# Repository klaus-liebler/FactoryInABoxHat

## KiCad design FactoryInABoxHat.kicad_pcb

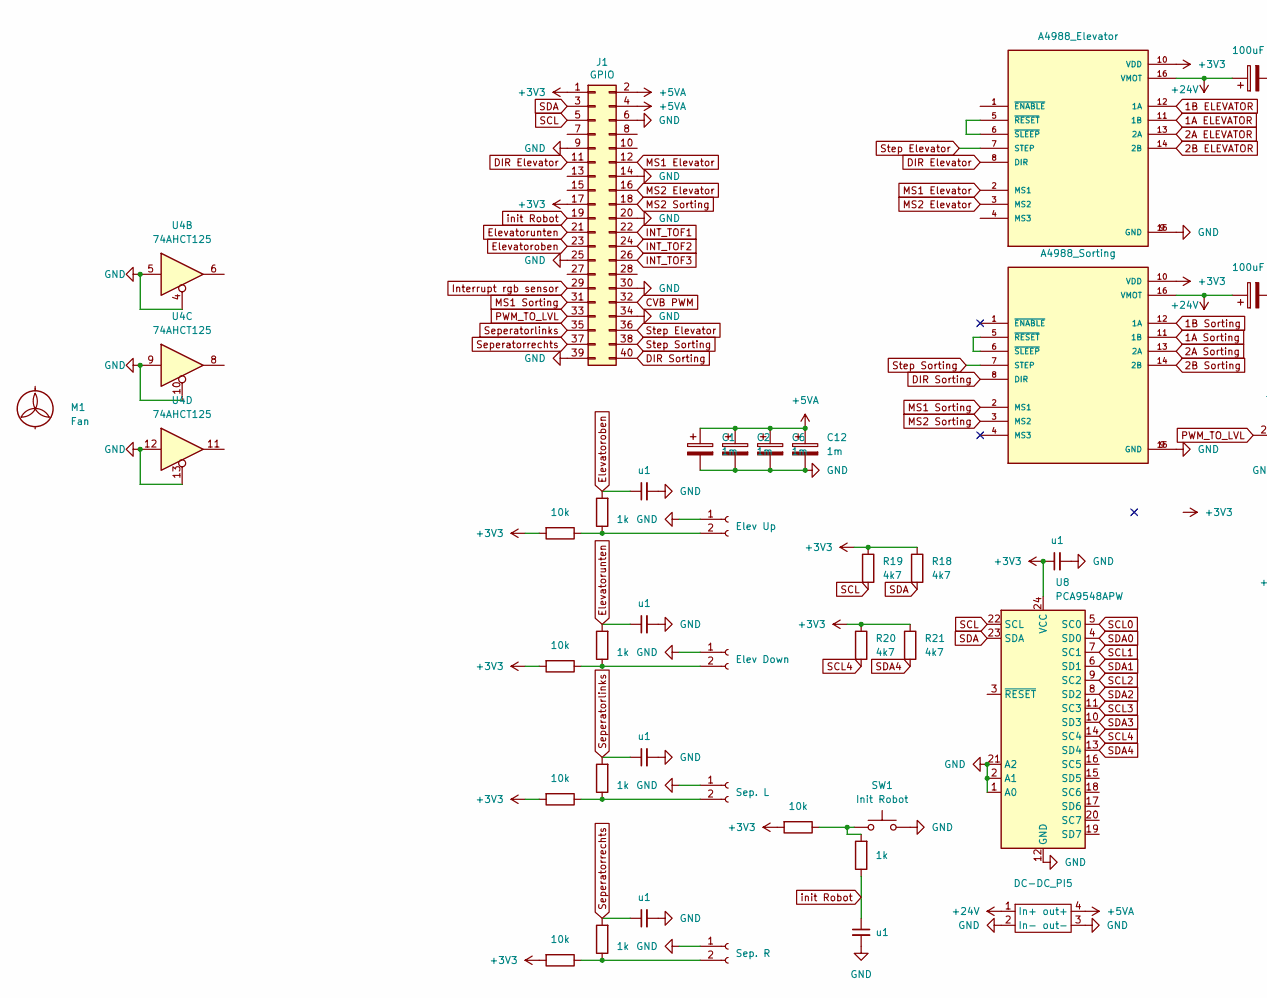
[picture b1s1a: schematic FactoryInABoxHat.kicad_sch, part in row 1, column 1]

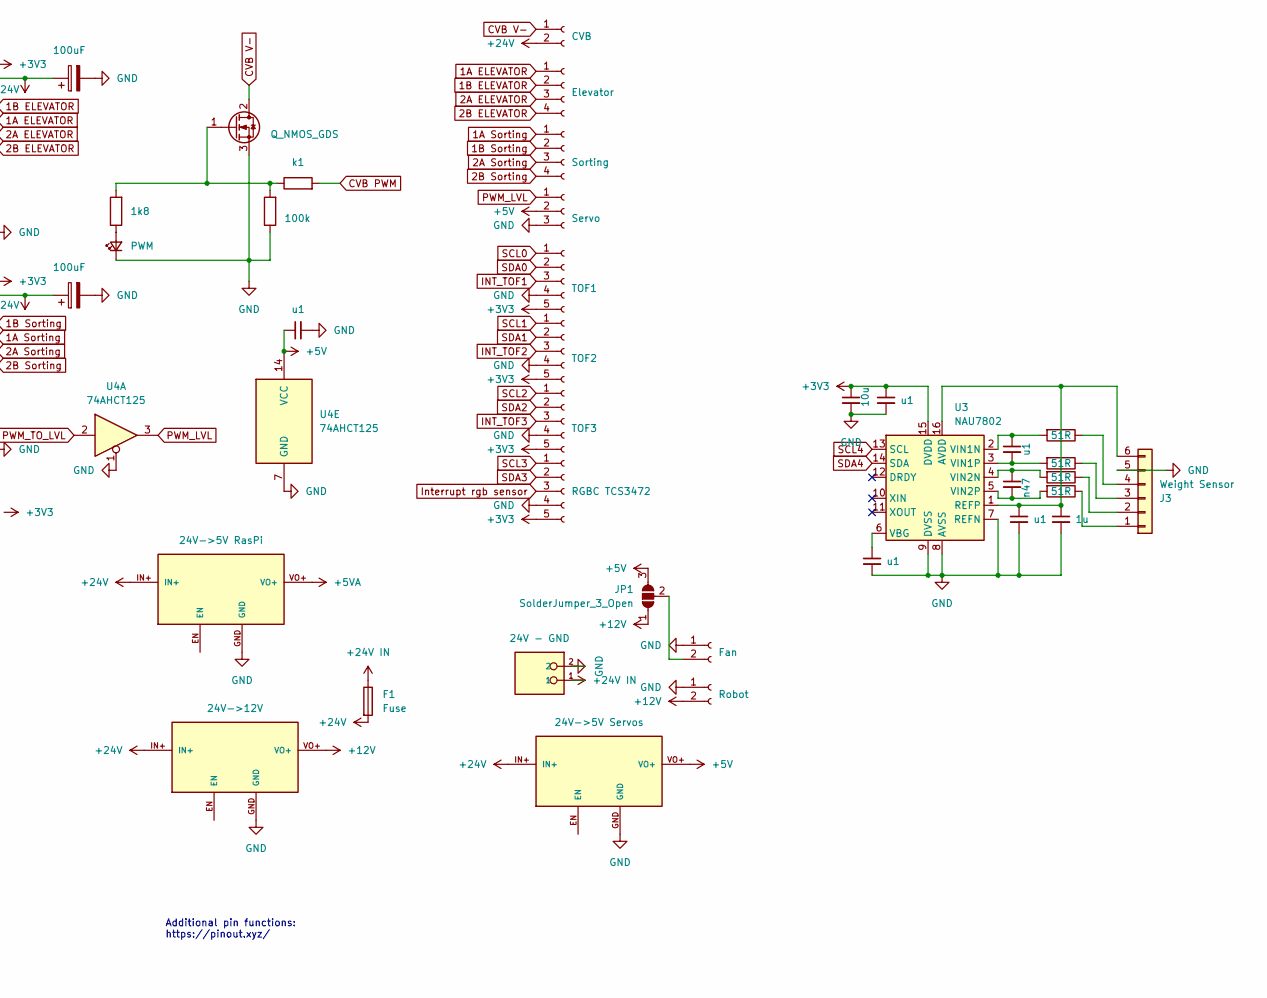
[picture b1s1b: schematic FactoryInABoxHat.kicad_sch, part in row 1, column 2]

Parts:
C1, C2, C6, C12: 1m; CP_Radial_D8.0mm_P5.00mm
C3, C7, C8, C9, C10, C11, C13, C14, C16, C18, C20: u1; C_0805_2012Metric_Pad1.18x1.45mm_HandSolder
C4, C5: 100uF; CP_Radial_D6.3mm_P2.50mm
C15: 1u; C_0805_2012Metric_Pad1.18x1.45mm_HandSolder
C17: 10u; C_0805_2012Metric_Pad1.18x1.45mm_HandSolder
C19: n47; C_0805_2012Metric_Pad1.18x1.45mm_HandSolder
D1: PWM; LED_0805_2012Metric_Pad1.15x1.40mm_HandSolder
DC-DC_PI5: DCDC-XL4015
F1: Fuse; Fuseholder_Cylinder-5x20mm_Schurter_0031_8201_Horizontal_Op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
J1: GPIO; PinSocket_2x20_P2.54mm_Vertical
J2: Servo; JST_XH_B3B-XH-A_1x03_P2.50mm_Vertical
J3: Weight Sensor; JST_XH_B6B-XH-A_1x06_P2.50mm_Vertical
J7: CVB; JST_XH_B2B-XH-A_1x02_P2.50mm_Vertical
J8: Elevator; JST_XH_B4B-XH-A_1x04_P2.50mm_Vertical
J9: RGBC TCS3472; JST_XH_B5B-XH-A_1x05_P2.50mm_Vertical
J10: Robot; JST_XH_B2B-XH-A_1x02_P2.50mm_Vertical
J11: Fan; JST_XH_B2B-XH-A_1x02_P2.50mm_Vertical
J12: Sep. L; JST_XH_B2B-XH-A_1x02_P2.50mm_Vertical
J13: Sorting; JST_XH_B4B-XH-A_1x04_P2.50mm_Vertical
J15: 24V - GND; TerminalBlock_Phoenix_MKDS-1,5-2-5.08_1x02_P5.08mm_Horizont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; PARTREV 28.07.2023
J17: TOF3; JST_XH_B5B-XH-A_1x05_P2.50mm_Vertical
J18: TOF2; JST_XH_B5B-XH-A_1x05_P2.50mm_Vertical
J19: TOF1; JST_XH_B5B-XH-A_1x05_P2.50mm_Vertical
J20: Elev Up; JST_XH_B2B-XH-A_1x02_P2.50mm_Vertical
J21: Elev Down; JST_XH_B2B-XH-A_1x02_P2.50mm_Vertical
J22: Sep. R; JST_XH_B2B-XH-A_1x02_P2.50mm_Vertical
JP1: SolderJumper_3_Open; SolderJumper-3_P1.3mm_Open_RoundedPad1.0x1.5mm
M1: Fan; FAN2507
Q3: Q_NMOS_GDS; TO-220-3_Vertical
R1: k1; R_0805_2012Metric_Pad1.20x1.40mm_HandSolder
R2: 1k8; R_0805_2012Metric_Pad1.20x1.40mm_HandSolder
R3: 100k; R_0805_2012Metric_Pad1.20x1.40mm_HandSolder
R4, R5, R6, R17: 51R; R_0805_2012Metric_Pad1.20x1.40mm_HandSolder
R7, R9, R11, R13, R16: 10k; R_0805_2012Metric_Pad1.20x1.40mm_HandSolder
R8, R10, R12, R14, R15: 1k; R_0805_2012Metric_Pad1.20x1.40mm_HandSolder
R18, R19, R20, R21: 4k7; R_0805_2012Metric_Pad1.20x1.40mm_HandSolder
SW1: Init Robot; SW_PUSH_6mm
U1: A4988_Elevator; MODULE_A4988_STEPPER_MOTOR_DRIVER_CARRIER
U2: A4988_Sorting; MODULE_A4988_STEPPER_MOTOR_DRIVER_CARRIER
U3: NAU7802; SOP-16_3.9x9.9mm_P1.27mm
U4: 74AHCT125
U5: 24V->5V Servos; DCDC_HW613
U6: 24V->12V; DCDC_HW613
U7: 24V->5V RasPi; DCDC_HW613
U8: PCA9548APW; TSSOP-24_4.4x7.8mm_P0.65mm

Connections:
1A ELEVATOR: J8.1, U1.11 (1B)
1A Sorting: J13.1, U2.11 (1B)
1B ELEVATOR: J8.2, U1.12 (1A)
1B Sorting: J13.2, U2.12 (1A)
2A ELEVATOR: J8.3, U1.13 (2A)
2A Sorting: J13.3, U2.13 (2A)
2B ELEVATOR: J8.4, U1.14 (2B)
2B Sorting: J13.4, U2.14 (2B)
+3V3: C11.1, C16.1, C17.1, J1.1, J1.17, J9.5, J17.5, J18.5, J19.5, R7.2, R9.2, R11.2, R13.2, R16.2, R18.1, R19.1, R20.1, R21.1, U1.10 (VDD), U2.10 (VDD), U3.15 (DVDD), U8.24 (VCC)
+5V: C20.1, J2.2, JP1.3 (B), U4.14 (VCC), U5.VO+
+5VA: C1.1, C2.1, C6.1, C12.1, DC-DC_PI5.4 (out+), J1.2, J1.4, U7.VO+
+12V: J10.2, JP1.1 (A), U6.VO+
+24V: C4.1, C5.1, DC-DC_PI5.1 (In+), F1.2, J7.2, U1.16 (VMOT), U2.16 (VMOT), U5.IN+, U6.IN+, U7.IN+
+24V IN: F1.1, J15.1
CVB PWM: J1.32, R1.2
CVB V-: J7.1, Q3.2 (D)
DIR Elevator: J1.11, U1.8 (DIR)
DIR Sorting: J1.40, U2.8 (DIR)
Elevatoroben: C7.1, J1.23, R10.2
Elevatorunten: C8.1, J1.21, R12.2
GND: C1.2, C2.2, C3.2, C4.2, C5.2, C6.2, C7.2, C8.2, C9.2, C10.2, C11.2, C12.2, C13.2, C14.2, C15.2, C16.2, C17.2, C20.2, D1.1 (K), DC-DC_PI5.2 (In-), DC-DC_PI5.3 (out-), J1.6, J1.9, J1.14, J1.20, J1.25, J1.30, J1.34, J1.39, J2.3, J3.5, J9.4, J10.1, J11.1, J12.1, J15.2, J17.4, J18.4, J19.4, J20.1, J21.1, J22.1, Q3.3 (S), R3.1, SW1.2, U1.9 (GND), U1.15 (GND), U2.9 (GND), U2.15 (GND), U3.7 (REFN), U3.8 (AVSS), U3.9 (DVSS), U4.1, U4.4, U4.5, U4.7 (GND), U4.9, U4.10, U4.12, U4.13, U5.GND, U6.GND, U7.GND, U8.1 (A0), U8.2 (A1), U8.12 (GND), U8.21 (A2)
INT_TOF1: J1.22, J19.3
INT_TOF2: J1.24, J18.3
INT_TOF3: J1.26, J17.3
Interrupt rgb sensor: J1.29, J9.3
MS1 Elevator: J1.12, U1.2 (MS1)
MS1 Sorting: J1.31, U2.2 (MS1)
MS2 Elevator: J1.16, U1.3 (MS2)
MS2 Sorting: J1.18, U2.3 (MS2)
unnamed: D1.2 (A), R2.1
unnamed: J3.1, R17.1
unnamed: J3.2, R6.1
unnamed: J3.3, R5.1
unnamed: J3.4, R4.1
unnamed: C14.1, C15.1, J3.6, U3.1 (REFP), U3.16 (AVDD)
unnamed: J11.2, JP1.2 (C)
unnamed: J12.2, R7.1, R8.1
unnamed: J20.2, R9.1, R10.1
unnamed: J21.2, R11.1, R12.1
unnamed: J22.2, R13.1, R14.1
unnamed: Q3.1 (G), R1.1, R2.2, R3.2
unnamed: R15.2, R16.1, SW1.1
unnamed: U1.5 (~RESET), U1.6 (~SLEEP)
unnamed: U2.5 (~RESET), U2.6 (~SLEEP)
unnamed: C13.1, U3.6 (VBG)
unnamed: C18.1, R4.2, U3.2 (VIN1N)
unnamed: C18.2, R5.2, U3.3 (VIN1P)
unnamed: C19.1, R6.2, U3.4 (VIN2N)
unnamed: C19.2, R17.2, U3.5 (VIN2P)
PWM_LVL: J2.1, U4.3
PWM_TO_LVL: J1.33, U4.2
SCL: J1.5, R19.2, U8.22 (SCL)
SCL0: J19.1, U8.5 (SC0)
SCL1: J18.1, U8.7 (SC1)
SCL2: J17.1, U8.9 (SC2)
SCL3: J9.1, U8.11 (SC3)
SCL4: R20.2, U3.13 (SCL), U8.14 (SC4)
SDA: J1.3, R18.2, U8.23 (SDA)
SDA0: J19.2, U8.4 (SD0)
SDA1: J18.2, U8.6 (SD1)
SDA2: J17.2, U8.8 (SD2)
SDA3: J9.2, U8.10 (SD3)
SDA4: R21.2, U3.14 (SDA), U8.13 (SD4)
Seperatorlinks: C3.1, J1.35, R8.2
Seperatorrechts: C9.1, J1.37, R14.2
Step Elevator: J1.36, U1.7 (STEP)
Step Sorting: J1.38, U2.7 (STEP)
init Robot: C10.1, J1.19, R15.1

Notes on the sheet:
Additional pin functions: https://pinout.xyz/

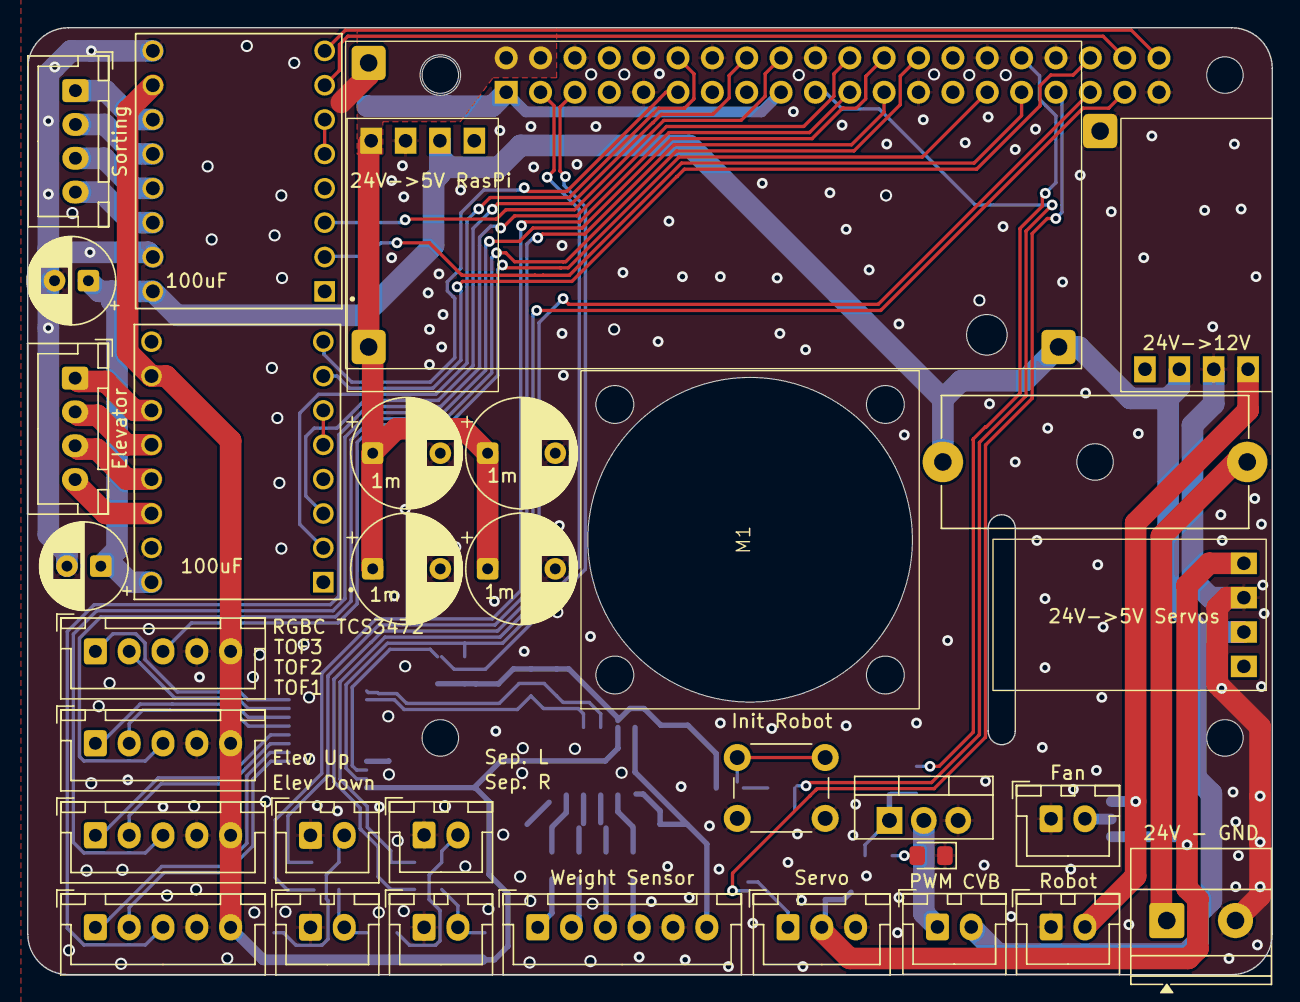
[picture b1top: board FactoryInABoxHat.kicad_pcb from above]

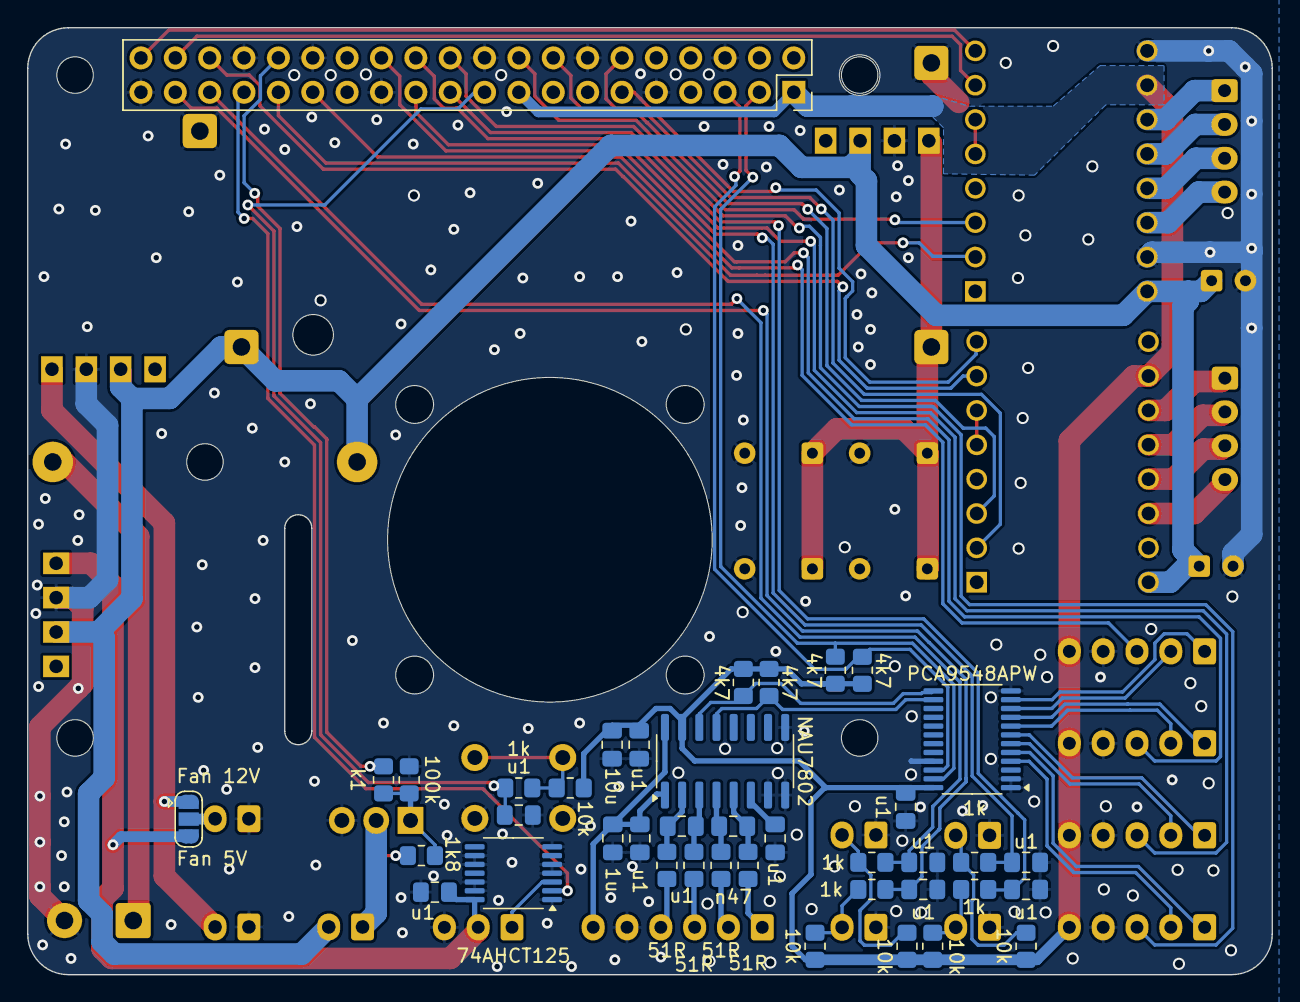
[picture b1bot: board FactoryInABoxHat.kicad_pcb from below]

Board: 2 copper layers, 92.0 x 70.0 mm, 77 parts (40 on the bottom side), 68 nets.

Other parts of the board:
MH1, MH2, MH3, MH4: MountingHole_2.7mm_M2.5
